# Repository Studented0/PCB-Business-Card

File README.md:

[PCB Business Card-bom.csv](https://github.com/user-attachments/files/27329266/PCB.Business.Card-bom.csv)
# PCB-Business-Card
 
A PCB Business card that shows your Spotify activity using lanyard in real time. Tap the card with a phone to show what song is playing on Spotify.
 
Powered over USB-C from a phone or any power bank. Connects to a phone hotspot (or any wifi) for the Lanyard WebSocket. 
 
## Screenshots

## Why I built this
 
I wanted a business card that has a cool twist. Plain cards feel boring to show and they are all the same. This one shows what I'm listening to, lets someone tap it to hear the same song, and has my GitHub a QR scan away. Business cards are supposed to grab people's attention, and I would say this one is different than other business cards.
 
## Hardware
 The ESP32 rewrites the NDEF URL every time a track changes over I2C, NT3H2111 (NFC Module) has I2C and RF interface simultaneously. When you are playing something NFC goes to spotify when nothing is playing goes to GitHub (for now). 100x75mm PCB. USB-C powers it with any power bank (im personally planning to use my phone). ESP32 is going to be hand soldered to save money but everything else is JLCPCB assembly 
 
## Wiring
 
| Signal | GPIO |
|--------|------|
| DISP_MOSI | IO11 |
| DISP_SCLK | IO12 |
| DISP_CS | IO10 |
| DISP_DC | IO13 |
| DISP_RST | IO14 |
| DISP_BLK | IO9 |
| NFC_SDA | IO5 |
| NFC_SCL | IO6 |
| NFC_FD | IO4 |
| USB_DN | IO19 |
| USB_DP | IO20 |
| BOOT | IO0 |
| RESET | EN |
 
## Firmware
 
`firmware/main.ino` 
 
Libraries needed: TFT_eSPI, TJpg_Decoder, ArduinoWebsockets, ArduinoJson. Board: ESP32S3 Dev Module.
 
## Bill of Materials
 
SMD parts assembled by JLCPCB. ESP32 and the display are sourced separately.
 
| Component | Qty | LCSC | Note |
|-----------|-----|------|------|
| 100nF 0402 cap | 3 | C1525 | Basic |
| 10µF 0805 cap | 2 | C15850 | Basic |
| 56pF 0402 cap | 1 | C107007 | Extended — antenna tuning |
| 5.1kΩ 0402 resistor | 2 | C25905 | Basic — USB-C CC |
| 10kΩ 0402 resistor | 3 | C25744 | Basic — pullups |
| 4.7kΩ 0402 resistor | 2 | C25900 | Basic — I2C pullups |
| AMS1117-3.3 SOT-223 | 1 | C6186 | Basic |
| NT3H2111W0FHKH XQFN-8 | 1 | C710403 | Extended — NFC |
| TYPE-C 16PIN 2MD | 1 | C2765186 | Extended — USB-C |
| Tactile switch SMD | 2 | — | Extended |
 Name,Purpose,Quantity,Total Cost (USD),Link,Distributor
"Display","Displaying",1,14.00,"https://www.amazon.com/gp/product/B0GL1SWYP4/ref=ox_sc_act_title_1?smid=A2Z10KY0342329&psc=1","Amazon"
"ESP32-S3-WROOM-1-N4","microcontroller",1,5.21,"https://www.digikey.com/en/products/detail/espressif-systems/ESP32-S3-WROOM-1-N4/16162639","DIGIKEY"
"JLCPCB","PCB",1,25.59,"","JLCPCB"
| Component | Qty | Source |
|-----------|-----|--------|
| ESP32-S3-WROOM-1-N8| 1 | Mouser Electronics |
| 2.0" ST7789V IPS 240×320 | 1 | Amazon |
 
## Repository Structure
 
```
PCB-Business-Card/
├── Firmware/
│   └── main.ino
├── lanyardpcbcard-backups/
├── libs/
│   └── easyeda/
│       ├── easyeda.3dshapes/
│       ├── easyeda.pretty/
│       └── easyeda.kicad_sym
├── production/
│   ├── backups/
│   ├── CPL-lanyardpcbcard.csv
│   ├── bom.csv
│   ├── lanyardpcbcard.step
│   ├── lanyardpcbcard.zip
│   └── ...
├── LICENSE
├── README.md
├── lanyardpcbcard.kicad_pcb
├── lanyardpcbcard.kicad_pro
├── lanyardpcbcard.kicad_sch
└── lanyardpcbcard.kicad_prl
```
 
## License
 
[MIT](LICENSE)

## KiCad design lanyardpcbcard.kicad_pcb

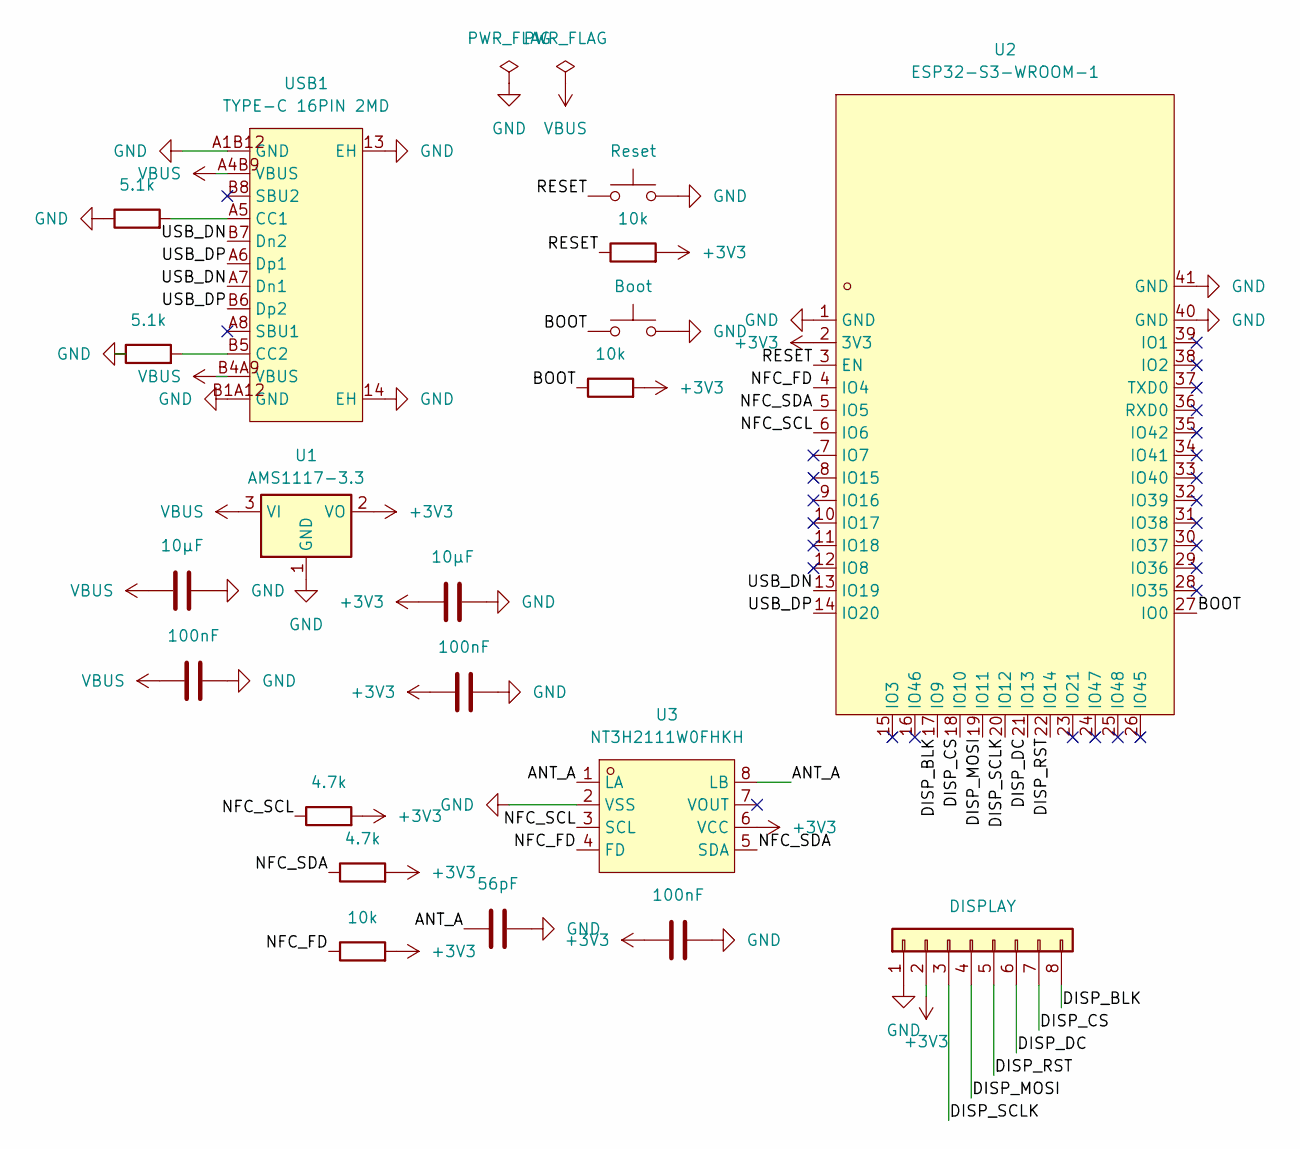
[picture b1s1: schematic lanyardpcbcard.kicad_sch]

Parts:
C1, C3: 10µF; C_0805_2012Metric
C2, C4, C5: 100nF; C_0402_1005Metric
C6: 56pF; C_0402_1005Metric
J1: DISPLAY; PinHeader_1x08_P2.54mm_Vertical
R1, R2: 5.1k; R_0402_1005Metric
R3, R4, R7: 10k; R_0402_1005Metric
R5, R6: 4.7k; R_0402_1005Metric
SW1: Reset; SW_Push_1TS009xxxx-xxxx-xxxx_6x6x5mm
SW2: Boot; SW_Push_1TS009xxxx-xxxx-xxxx_6x6x5mm
U1: AMS1117-3.3; SOT-223-3_TabPin2
U2: ESP32-S3-WROOM-1; WIRELM-SMD_ESP32-S3-WROOM-1; MPN ESP32-S3-WROOM-1-N16R8; LCSC Part C2913202
U3: NT3H2111W0FHKH; XQFN-8_L1.6-W1.6-P0.50-BL_NT3H2111W0FHKH; MPN NT3H2111W0FHKH; LCSC Part C710403
USB1: TYPE-C 16PIN 2MD; USB-C-SMD_TYPE-C-16PIN-2MD-073; MPN TYPE-C 16PIN 2MD(073); LCSC Part C2765186

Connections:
+3V3: C3.1, C4.1, C5.1, J1.2, R3.2, R4.2, R5.2, R6.2, R7.2, U1.2 (VO), U2.2 (3V3), U3.6 (VCC)
/ANT_A: C6.1, U3.1 (LA), U3.8 (LB)
/BOOT: R4.1, SW2.1, U2.27 (IO0)
/DISP_BLK: J1.8, U2.17 (IO9)
/DISP_CS: J1.7, U2.18 (IO10)
/DISP_DC: J1.6, U2.21 (IO13)
/DISP_MOSI: J1.4, U2.19 (IO11)
/DISP_RST: J1.5, U2.22 (IO14)
/DISP_SCLK: J1.3, U2.20 (IO12)
/NFC_FD: R7.1, U2.4 (IO4), U3.4 (FD)
/NFC_SCL: R5.1, U2.6 (IO6), U3.3 (SCL)
/NFC_SDA: R6.1, U2.5 (IO5), U3.5 (SDA)
/RESET: R3.1, SW1.1, U2.3 (EN)
/USB_DN: U2.13 (IO19), USB1.A7 (Dn1), USB1.B7 (Dn2)
/USB_DP: U2.14 (IO20), USB1.A6 (Dp1), USB1.B6 (Dp2)
GND: C1.2, C2.2, C3.2, C4.2, C5.2, C6.2, J1.1, R1.1, R2.1, SW1.2, SW2.2, U1.1 (GND), U2.1 (GND), U2.40 (GND), U2.41 (GND), U3.2 (VSS), USB1.13 (EH), USB1.14 (EH), USB1.A1B12 (GND), USB1.B1A12 (GND)
unnamed: R1.2, USB1.A5 (CC1)
unnamed: R2.2, USB1.B5 (CC2)
VBUS: C1.1, C2.1, U1.3 (VI), USB1.A4B9 (VBUS), USB1.B4A9 (VBUS)

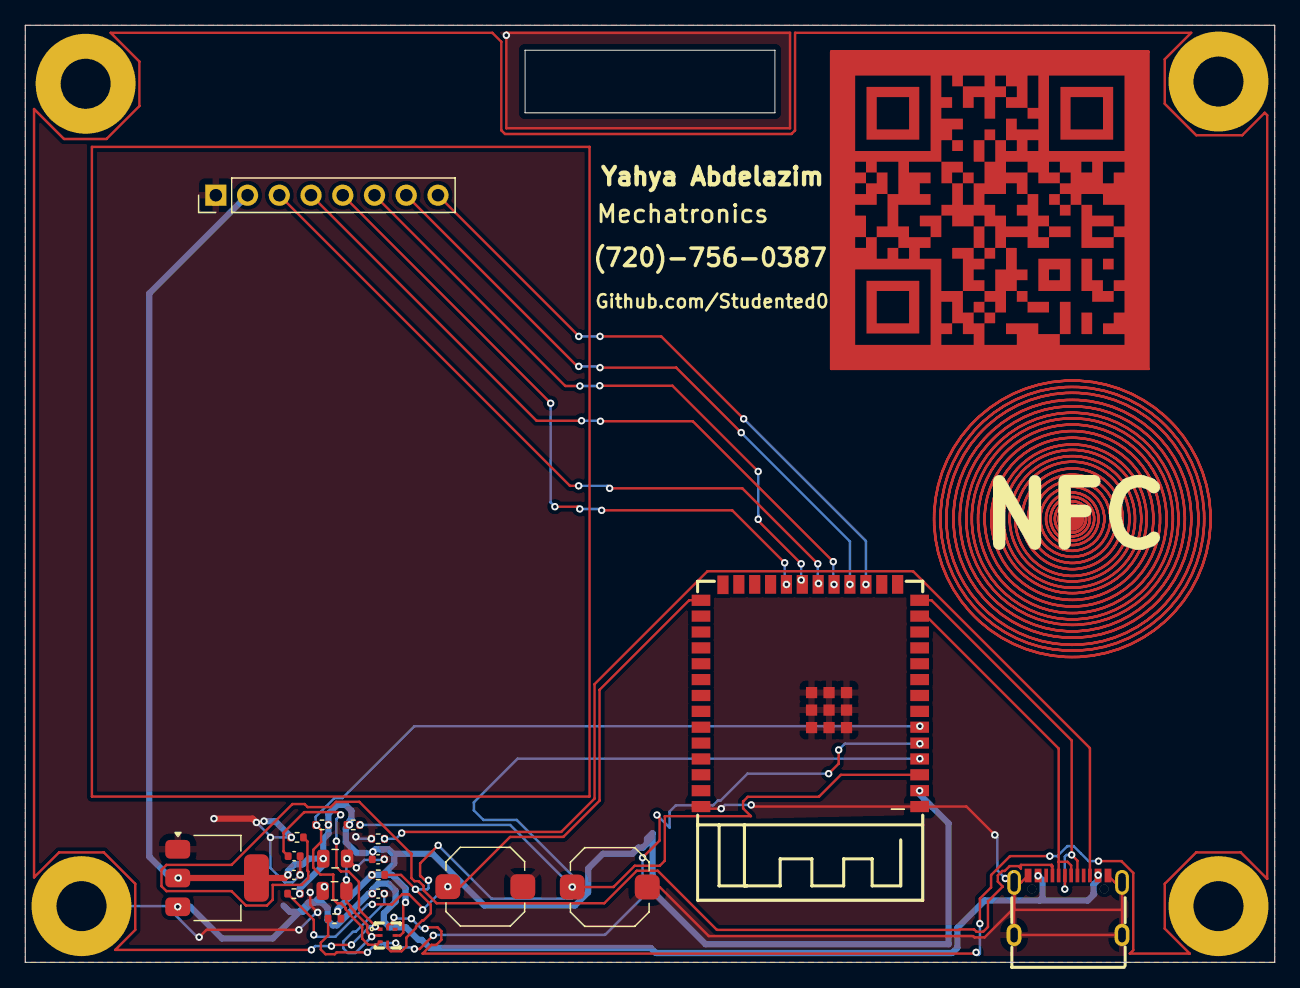
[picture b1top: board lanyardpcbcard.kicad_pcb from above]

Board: 2 copper layers, 100.0 x 75.0 mm, 20 parts (0 on the bottom side), 19 nets.

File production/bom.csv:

Designator,Footprint,Quantity,Value,LCSC Part #
"C1, C3",0805,2,10µF,
"C2, C4, C5",0402,3,100nF,
C6,0402,1,56pF,
J1,PinHeader_1x08_P2.54mm_Vertical,1,DISPLAY,
"R1, R2",0402,2,5.1k,
"R3, R4, R7",0402,3,10k,
"R5, R6",0402,2,4.7k,
SW1,SW_Push_1TS009xxxx-xxxx-xxxx_6x6x5mm,1,Reset,
SW2,SW_Push_1TS009xxxx-xxxx-xxxx_6x6x5mm,1,Boot,
U1,SOT-223-3_TabPin2,1,AMS1117-3.3,
U2,WIRELM-SMD_ESP32-S3-WROOM-1,1,ESP32-S3-WROOM-1,C2913202
U3,XQFN-8_L1.6-W1.6-P0.50-BL_NT3H2111W0FHKH,1,NT3H2111W0FHKH,C710403
USB1,USB-C-SMD_TYPE-C-16PIN-2MD-073,1,TYPE-C 16PIN 2MD,C2765186

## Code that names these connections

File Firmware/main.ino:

#include <Arduino.h>
#include <WiFi.h>
#include <WiFiClientSecure.h>
#include <ArduinoWebsockets.h>
#include <ArduinoJson.h>
#include <TFT_eSPI.h>
#include <TJpg_Decoder.h>
#include <HTTPClient.h>
#include <Wire.h>
#include <time.h>

#define NFC_SDA 5
#define NFC_SCL 6
#define NFC_FD  4

const char* WIFI_SSID = "YOUR_SSID";
const char* WIFI_PASS = "YOUR_PASSWORD";
const char* DISCORD_USER_ID = "YOUR_ID";
const char* GITHUB_URL = "https://github.com/Studented0";
const char* NTP_SERVER = "pool.ntp.org";

using namespace websockets;

TFT_eSPI tft = TFT_eSPI();
WebsocketsClient ws;

String currentTrackId = "";
String currentTitle = "";
String currentArtist = "";
String currentAlbumArt = "";
long timestampStart = 0;
long timestampEnd = 0;
bool isPlaying = false;

bool tftOutput(int16_t x, int16_t y, uint16_t w, uint16_t h, uint16_t* bitmap) {
    tft.pushImage(x, y, w, h, bitmap);
    return true;
}

void writeNFC(const char* url) {
    Wire.beginTransmission(0x55);
    Wire.endTransmission();
}

void fetchAndDisplayAlbumArt(String url) {
    HTTPClient http;
    http.begin(url);
    int code = http.GET();
    if (code == 200) {
        WiFiClient* stream = http.getStreamPtr();
        TJpgDec.drawJpg(0, 0, (const uint8_t*)stream, http.getSize());
    }
    http.end();
}

void displayNowPlaying() {
    tft.fillRect(0, 240, 240, 80, TFT_BLACK);
    tft.setTextColor(TFT_WHITE);
    tft.setTextSize(1);
    tft.setCursor(0, 245);
    tft.println(currentTitle);
    tft.println(currentArtist);
}

void displayProgressBar() {
    long now = time(nullptr) * 1000L;
    long progress = now - timestampStart;
    long duration = timestampEnd - timestampStart;
    int barWidth = map(progress, 0, duration, 0, 240);
    tft.fillRect(0, 310, barWidth, 4, TFT_GREEN);
    tft.fillRect(barWidth, 310, 240 - barWidth, 4, TFT_DARKGREY);
}

void displayIdle() {
    tft.fillScreen(TFT_BLACK);
    tft.setTextColor(TFT_WHITE);
    tft.setCursor(20, 100);
    tft.println("Yahya Abdelazim");
    tft.setCursor(20, 120);
    tft.println("github.com/Studented0");
    writeNFC(GITHUB_URL);
}

void handleLanyardMessage(WebsocketsMessage msg) {
    JsonDocument doc;
    deserializeJson(doc, msg.data());
    
    int op = doc["op"];
    
    if (op == 1) {
        ws.send("{\"op\":2,\"d\":{\"subscribe_to_id\":\"" + String(DISCORD_USER_ID) + "\"}}");
    }
    
    if (op == 0) {
        JsonObject spotify = doc["d"]["spotify"];
        
        if (spotify.isNull()) {
            isPlaying = false;
            displayIdle();
            return;
        }
        
        isPlaying = true;
        currentTitle = spotify["song"].as<String>();
        currentArtist = spotify["artist"].as<String>();
        currentAlbumArt = spotify["album_art_url"].as<String>();
        timestampStart = spotify["timestamps"]["start"].as<long>();
        timestampEnd = spotify["timestamps"]["end"].as<long>();
        
        String trackUrl = spotify["track_id"].as<String>();
        String nfcUrl = "https://open.spotify.com/track/" + trackUrl;
        writeNFC(nfcUrl.c_str());
        
        fetchAndDisplayAlbumArt(currentAlbumArt);
        displayNowPlaying();
    }
}

void setup() {
    Serial.begin(115200);
    
    Wire.begin(NFC_SDA, NFC_SCL);
    
    tft.init();
    tft.setRotation(0);
    tft.fillScreen(TFT_BLACK);
    
    TJpgDec.setJpgScale(1);
    TJpgDec.setCallback(tftOutput);
    
    WiFi.begin(WIFI_SSID, WIFI_PASS);
    while (WiFi.status() != WL_CONNECTED) delay(500);
    
    configTime(0, 0, NTP_SERVER);
    while (time(nullptr) < 1000) delay(100);
    
    ws.onMessage(handleLanyardMessage);
    ws.connect("wss://api.lanyard.rest/socket");
}

void loop() {
    ws.poll();
    
    if (isPlaying) {
        displayProgressBar();
    }
    
    if (WiFi.status() != WL_CONNECTED) {
        WiFi.reconnect();
    }
    
    if (!ws.available()) {
        ws.connect("wss://api.lanyard.rest/socket");
    }
    
    delay(100);
}

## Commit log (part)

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2026-05-04 Initial design files - schematic, PCB layout, firmware skeleton
2026-05-04 Enhance README with detailed project information
    Expanded the README to provide detailed information about the PCB business card features, hardware specifications, NFC functionality, progress bar calculations, wiring details, firmware requirements,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
2026-05-04 Enhance README with new screenshot and license link
    Updated README to include a new image and corrected license formatting.
2026-05-04 Replace PDF link with images in README
    Updated the README to include images instead of a PDF link.
2026-05-04 Update README with BOM link and component details
    Added a link to the BOM CSV file and updated the components table with additional details.
2026-05-05 Regenerated production files, rounded corners, updated BOM
